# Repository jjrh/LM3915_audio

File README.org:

* about
  Second PCB I have designed, this time in kicad.

  Again it is being sent to Seeedstudio for manufacturing.

* Audio Power Meter with LM3915 IC.
  Design is from http://www.ti.com/lit/ds/symlink/lm3915.pdf
  Fig.39 (page 26)

  #+CAPTION: schematic
#+NAME:   fig:1
#+attr_html: :width 800px
[[./images/Audio_Power_Meter.sch.png]]

  #+CAPTION: 3d render
#+NAME:   fig:2
#+attr_html: :width 800px
[[./images/Audio_Power_Meter.png]]

  #+CAPTION: PCB
#+NAME:   fig:3
#+attr_html: :width 800px
[[./images/g708.png]]

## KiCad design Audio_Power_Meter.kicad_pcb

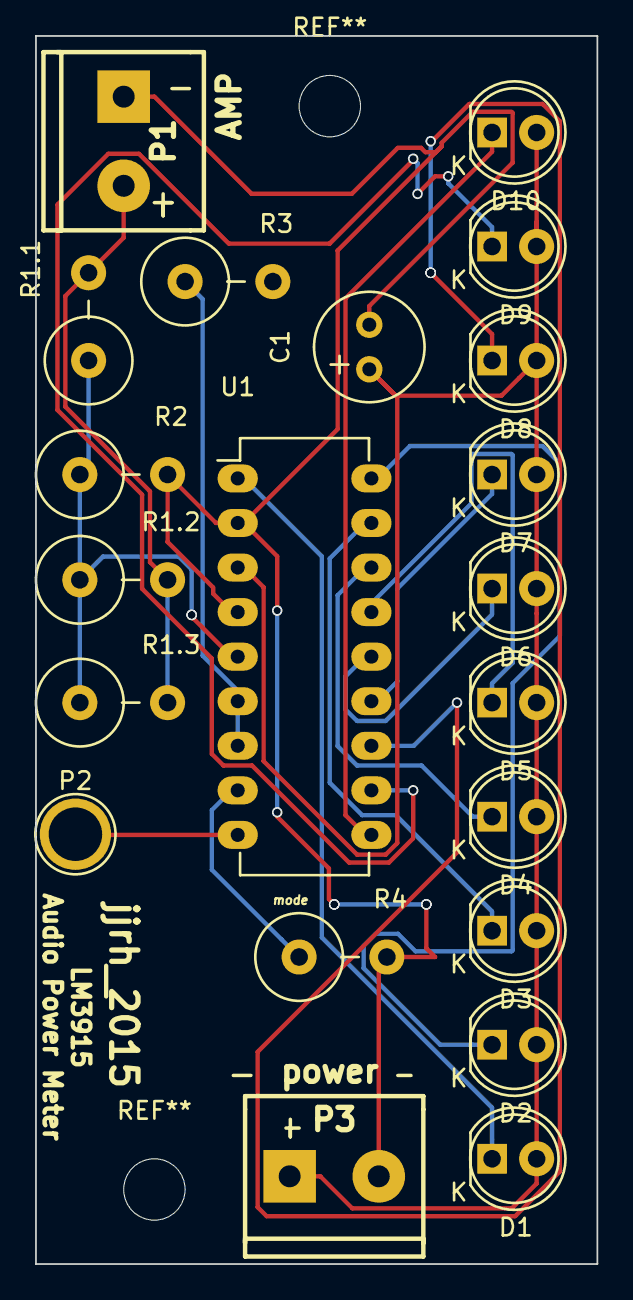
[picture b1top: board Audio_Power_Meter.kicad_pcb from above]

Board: 2 copper layers, 32.0 x 70.0 mm, 21 parts (0 on the bottom side), 17 nets.

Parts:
C1: 2.2; Elko_vert_11.2x6.3mm_RM2.5
D1, D2, D3, D4, D5, D6, D7, D8, D9, D10: LED; LED-5MM
P1: AMP; mors_2p
P2: CONN_01X01; 1pin
P3: power; mors_2p
R1.1, R2: 10k; Resistor_Vertical_RM5mm
R1.2: 18k; Resistor_Vertical_RM5mm
R1.3: 30k; Resistor_Vertical_RM5mm
R3: 390; Resistor_Vertical_RM5mm
R4: 2.7k; Resistor_Vertical_RM5mm
U1: LM3915; DIP-18_W7.62mm_LongPads

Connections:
+12V: C1.1, D1.2, D2.2, D3.2, D4.2, D5.2, D6.2, D7.2, D8.2, D9.2, D10.2, P3.1, U1.3
GND: C1.2, P1.1, P3.2, R2.2, R4.2, U1.2, U1.4
unnamed: D1.1, U1.1
unnamed: D2.1, U1.18
unnamed: D3.1, U1.17
unnamed: D4.1, U1.16
unnamed: D5.1, U1.15
unnamed: D6.1, U1.14
unnamed: D7.1, U1.13
unnamed: D8.1, U1.12
unnamed: D9.1, U1.11
unnamed: D10.1, U1.10
unnamed: P1.2, R1.1.2, R1.2.2, R1.3.2
unnamed: P2.1, U1.9
unnamed: R1.1.1, R1.2.1, R1.3.1, R2.1, U1.5
unnamed: R3.1, U1.6, U1.7
unnamed: R3.2, R4.1, U1.8

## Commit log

2015-07-05 made pcb page size smaller for exporty
2015-07-05 more image exports
2015-07-05 added readme
2015-07-05 changed svgs to images so they render on github
2015-07-05 optimized the size of the pcb svg
2015-07-05 various svg image chagnes
